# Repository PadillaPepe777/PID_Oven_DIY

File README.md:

In this project We'll build a PID Controlled Oven with a custom circuit board to modify a simple electric oven, 
with a ramp function to increase and decrease temperature at a desired rate, and a soak function to stay at a 
temperature the established time.

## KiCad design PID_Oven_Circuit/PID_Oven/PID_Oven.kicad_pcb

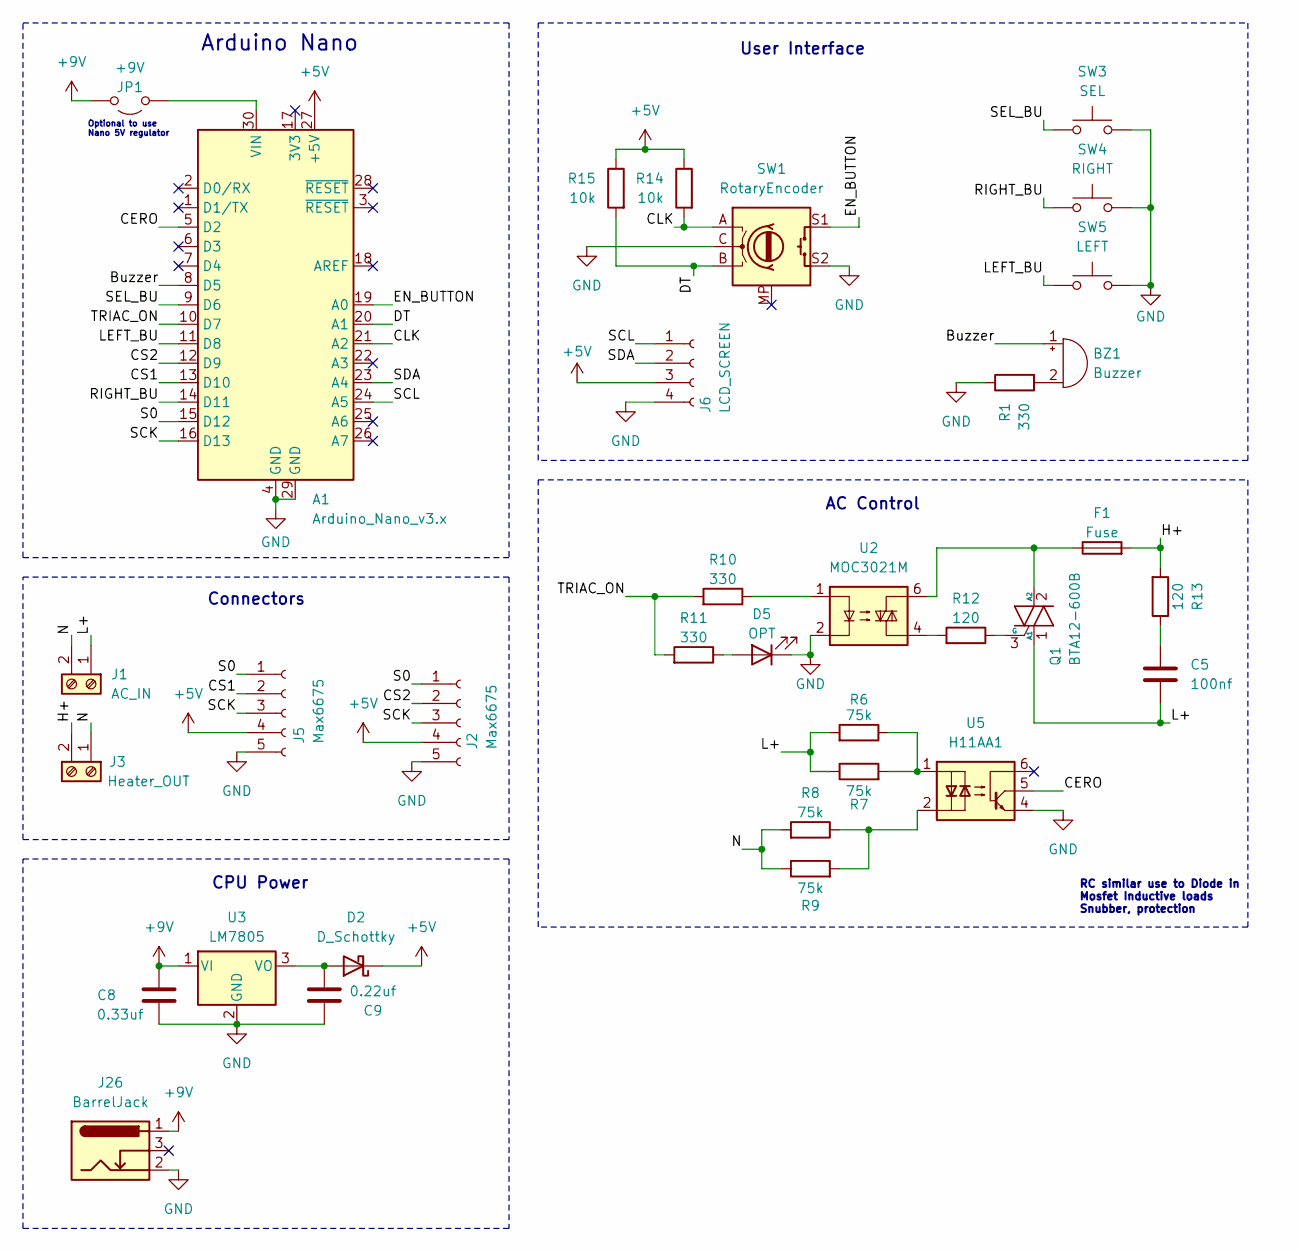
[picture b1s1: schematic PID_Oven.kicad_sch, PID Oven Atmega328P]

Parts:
A1: Arduino_Nano_v3.x; ArduinoNano
BZ1: Buzzer; Buzzer_12x9.5RM7.6
C5: 100nf; C_Disc_D5.0mm_W2.5mm_P5.00mm
C8: 0.33uf; C_Disc_D5.0mm_W2.5mm_P5.00mm
C9: 0.22uf; C_Disc_D5.0mm_W2.5mm_P5.00mm
D2: D_Schottky; D_SMA
D5: OPT; LED_D5.0mm_FlatTop
F1: Fuse; Fuse_Schurter_UMZ250
J1: AC_IN; TerminalBlock_MaiXu_MX126-5.0-02P_1x02_P5.00mm
J2, J5: Max6675; PinHeader_1x05_P2.54mm_Vertical
J3: Heater_OUT; TerminalBlock_MaiXu_MX126-5.0-02P_1x02_P5.00mm
J6: LCD_SCREEN; PinSocket_1x04_P2.54mm_Vertical
J26: BarrelJack; BarrelJack_GCT_DCJ200-10-A_Horizontal
JP1: +9V; SolderJumper-2_P1.3mm_Open_RoundedPad1.0x1.5mm
Q1: BTA12-600B; TO-220-3_Vertical
R1, R10, R11: 330; R_Axial_DIN0207_L6.3mm_D2.5mm_P10.16mm_Horizontal
R6, R7, R8, R9: 75k; R_Axial_DIN0207_L6.3mm_D2.5mm_P10.16mm_Horizontal
R12, R13: 120; R_Axial_DIN0207_L6.3mm_D2.5mm_P10.16mm_Horizontal
R14, R15: 10k; R_Axial_DIN0207_L6.3mm_D2.5mm_P10.16mm_Horizontal
SW1: RotaryEncoder; RotaryEncoder_Alps_EC11E-Switch_Vertical_H20mm
SW3: SEL; SW_PUSH_6mm
SW4: RIGHT; SW_PUSH_6mm
SW5: LEFT; SW_PUSH_6mm
U2: MOC3021M; DIP-6_W7.62mm
U3: LM7805; TO-220-3_Vertical
U5: H11AA1; DIP-6_W7.62mm

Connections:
+5V: A1.27 (+5V), D2.1 (K), J2.4, J5.4, J6.3, R14.1, R15.1
+9V: C8.1, J26.1, JP1.2 (B), U3.1 (VI)
/Buzzer: A1.8 (D5), BZ1.1 (+)
/CERO: A1.5 (D2), U5.5
/CLK: A1.21 (A2), R14.2, SW1.A
/CS1: A1.13 (D10), J5.2
/CS2: A1.12 (D9), J2.2
/DT: A1.20 (A1), R15.2, SW1.B
/EN_BUTTON: A1.19 (A0), SW1.S1
/H+: F1.2, J3.2, R13.2
/L+: C5.2, J1.1, Q1.1 (A1), R6.2, R7.1
/LEFT_BU: A1.11 (D8), SW5.1
/N: J1.2, J3.1, R8.2, R9.1
/RIGHT_BU: A1.14 (D11), SW4.1
/S0: A1.15 (D12), J2.1, J5.1
/SCK: A1.16 (D13), J2.3, J5.3
/SCL: A1.24 (A5), J6.1
/SDA: A1.23 (A4), J6.2
/SEL_BU: A1.9 (D6), SW3.1
/TRIAC_ON: A1.10 (D7), R10.2, R11.2
GND: A1.4 (GND), A1.29 (GND), C8.2, C9.1, D5.1 (K), J2.5, J5.5, J6.4, J26.2, R1.1, SW1.C, SW1.S2, SW3.2, SW4.2, SW5.2, U2.2, U3.2 (GND), U5.4
unnamed: A1.30 (VIN), JP1.1 (A)
unnamed: BZ1.2 (-), R1.2
unnamed: C5.1, R13.1
unnamed: C9.2, D2.2 (A), U3.3 (VO)
unnamed: D5.2 (A), R11.1
unnamed: F1.1, Q1.2 (A2), U2.6
unnamed: Q1.3 (G), R12.1
unnamed: R6.1, R7.2, U5.1
unnamed: R8.1, R9.2, U5.2
unnamed: R10.1, U2.1
unnamed: R12.2, U2.4

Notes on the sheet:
Optional to use Nano 5V regulator
User Interface
CPU Power
AC Control
Connectors
Arduino Nano
RC similar use to Diode in Mosfet Inductive loads Snubber, protection

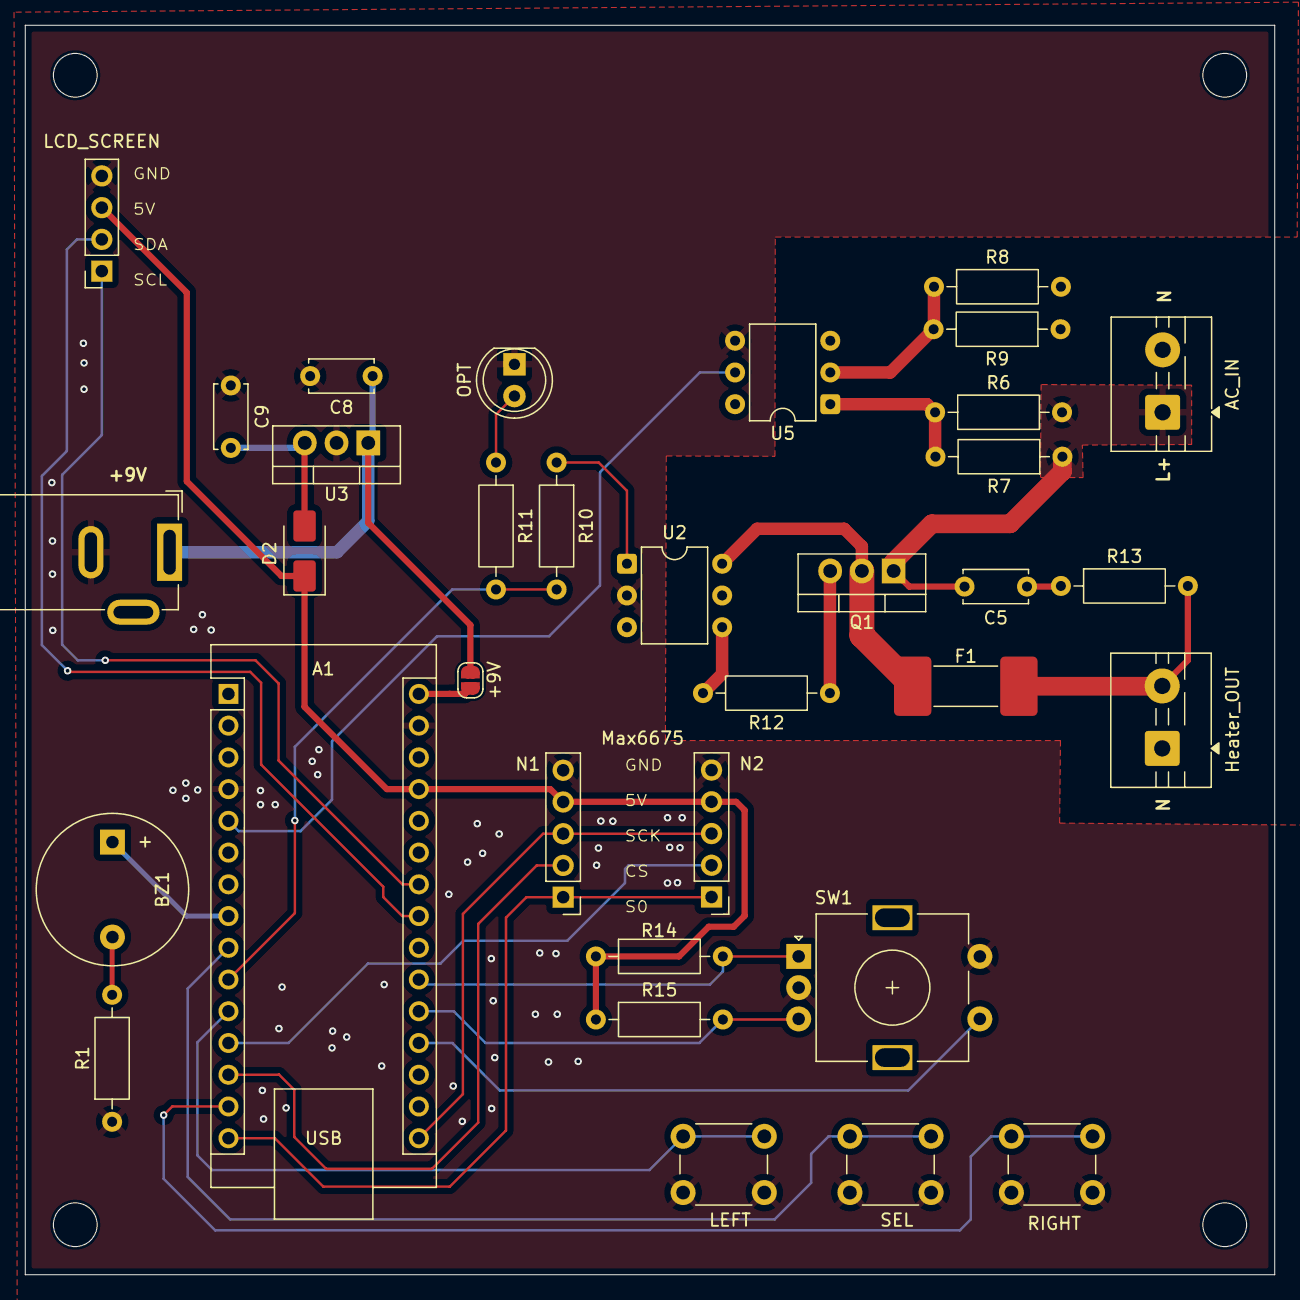
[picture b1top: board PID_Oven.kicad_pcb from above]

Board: 2 copper layers, 100.0 x 100.0 mm, 34 parts (0 on the bottom side), 32 nets.
